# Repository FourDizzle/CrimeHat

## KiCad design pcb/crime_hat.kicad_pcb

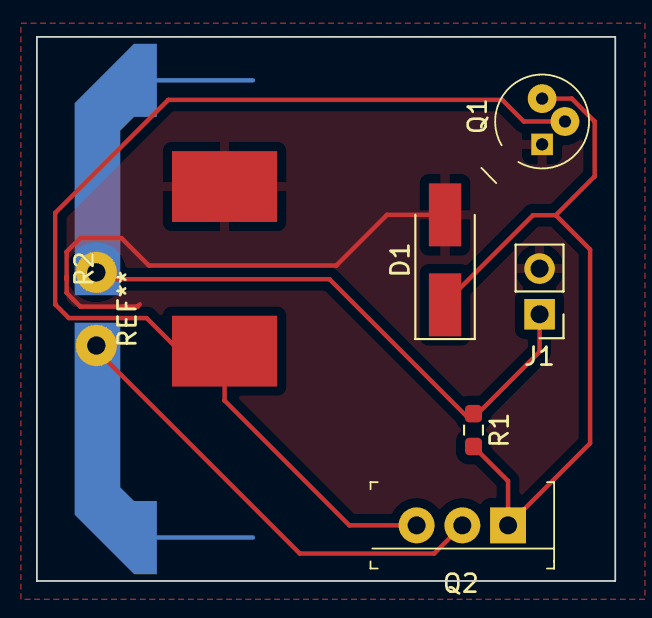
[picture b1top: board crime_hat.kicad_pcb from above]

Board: 2 copper layers, 32.1 x 30.2 mm, 6 parts (0 on the bottom side), 4 nets.

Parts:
D1: 1N4733A; D_SMA_Handsoldering
J1: Conn_01x02_Male; PinHeader_1x02_P2.54mm_Vertical
Q1: 2N2222; TO-18-3
Q2: FQP27P06; TO-220-3
R1: FQP50N06L; R_0603_1608Metric_Pad0.98x0.95mm_HandSolder
R2: 49.9R; Resistor-WSC000249R90FEB

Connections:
+9VA: J1.1, R1.1
GND: D1.2 (A), J1.2, Q1.1 (E), R2.2
unnamed: D1.1 (K), Q1.3 (C), Q2.1 (G), R1.2
unnamed: Q1.2 (B), Q2.3 (S), R2.1

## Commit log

2022-02-08 init commit
2022-02-19 layout
